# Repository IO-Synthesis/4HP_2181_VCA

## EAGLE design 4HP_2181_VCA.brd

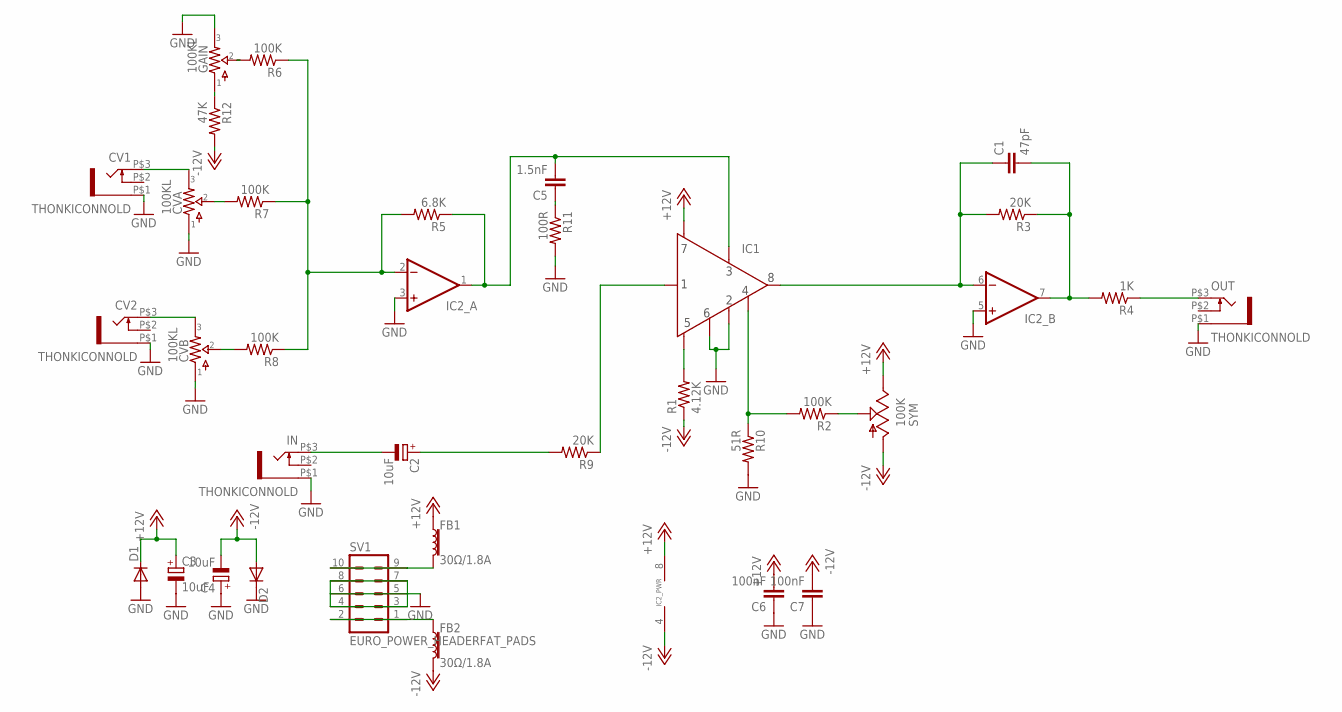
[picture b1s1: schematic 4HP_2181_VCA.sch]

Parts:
C1: 47pF; 0603-CAP
C2, C3, C4: 10uF; CASE_B
C5: 1.5nF; 0603-CAP
C6, C7: 100nF; 0603-CAP
CV1, CV2: THONKICONNOLD; THONKICONN
CVA: 100KL; 9MM_W/MOUNTS-2MMHOLES
CVB: 100KL; 9MM_W/MOUNTS-2MMHOLES
D1, D2: DIODE-SOD-123; SOD-123
FB1, FB2: 30Ω/1.8A; 0603
GAIN: 100KL; 9MM_W/MOUNTS-2MMHOLES
IC1: THAT2181C; SIL8
IC2: DUALSMD; SO08
IN: THONKICONNOLD; THONKICONN
OUT: THONKICONNOLD; THONKICONN
R1: 4.12K; 0603-RES
R2, R6, R7, R8: 100K; 0603-RES
R3, R9: 20K; 0603-RES
R4: 1K; 0603-RES
R5: 6.8K; 0603-RES
R10: 51R; 0603-RES
R11: 100R; 0603-RES
R12: 47K; 0603-RES
SV1: EURO_POWER_HEADERFAT_PADS; EURO_PWR_HEADER_FAT
SYM: 100K; S64W

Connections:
+12V: C3.+, C6.2, D1.C, FB1.1, IC1.7, IC2.8 (V+), SYM.E
-12V: C4.-, C7.2, D2.A, FB2.2, IC2.4 (V-), R1.1, R12.2, SYM.A
GND: C3.-, C4.+, C6.1, C7.1, CV1.P$1 (5), CV2.P$1 (5), CVA.P$1 (1), CVB.P$1 (1), D1.A, D2.C, GAIN.P$3 (3), IC1.2, IC1.6, IC2.3 (+IN), IC2.5 (+IN), IN.P$1 (5), OUT.P$1 (5), R10.2, R11.2, SV1.3, SV1.4, SV1.5, SV1.6, SV1.7, SV1.8
unnamed: C1.1, IC1.8, IC2.6 (-IN), R3.2
unnamed: C5.2, IC1.3, IC2.1 (OUT), R5.1
unnamed: IC1.5, R1.2
unnamed: C1.2, IC2.7 (OUT), R3.1, R4.2
unnamed: IC1.4, R2.2, R10.1
unnamed: R2.1, SYM.S
unnamed: OUT.P$3 (3), R4.1
unnamed: GAIN.P$2 (2), R6.2
unnamed: CVA.P$2 (2), R7.2
unnamed: CVB.P$2 (2), R8.2
unnamed: IC2.2 (-IN), R5.2, R6.1, R7.1, R8.1
unnamed: C2.+, R9.2
unnamed: C2.-, IN.P$3 (3)
unnamed: IC1.1, R9.1
unnamed: CV1.P$3 (3), CVA.P$3 (3)
unnamed: CV2.P$3 (3), CVB.P$3 (3)
unnamed: FB1.2, SV1.9, SV1.10
unnamed: FB2.1, SV1.1, SV1.2
unnamed: C5.1, R11.1
unnamed: GAIN.P$1 (1), R12.1

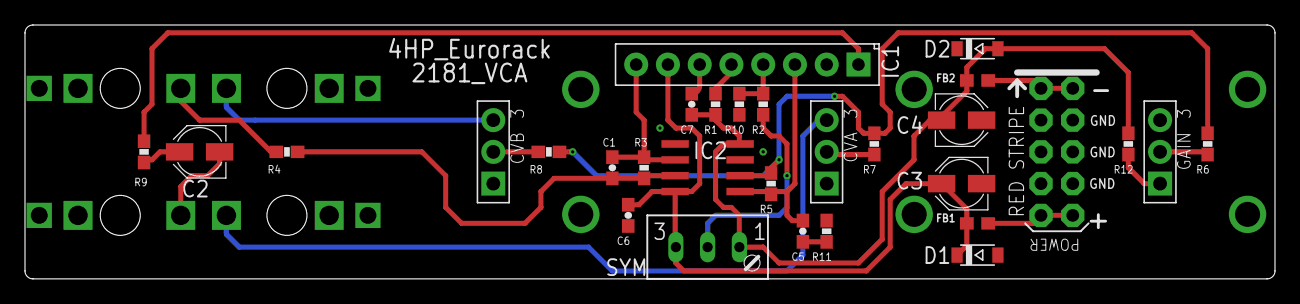
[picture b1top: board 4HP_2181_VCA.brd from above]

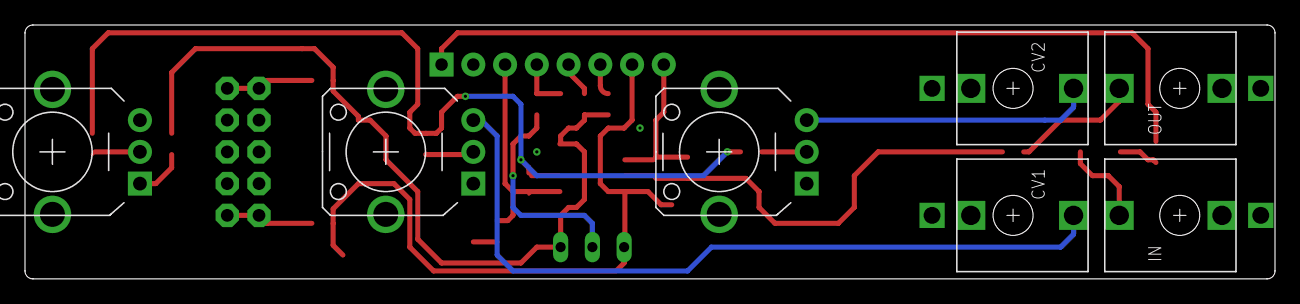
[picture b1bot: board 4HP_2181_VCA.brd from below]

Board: 2 copper layers, 100.0 x 20.3 mm, 34 parts (4 on the bottom side), 23 nets.

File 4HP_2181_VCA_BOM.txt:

Partlist exported from C:/Users/Erik/Documents/GitHub/4HP_2181_VCA/4HP_2181_VCA.sch at 4/30/2017 8:24 AM

Part Value                     Device                    Package               Description                                       PROD_ID    VALUE   
C1   47pF                      CAP0603-CAP               0603-CAP              Capacitor                                                            
C2   10uF                      CAPACITOR_POL-CASE_B      CASE_B                Polarized capacitor in various packages                              
C3   10uF                      CAPACITOR_POL-CASE_B      CASE_B                Polarized capacitor in various packages                              
C4   10uF                      CAPACITOR_POL-CASE_B      CASE_B                Polarized capacitor in various packages                              
C5   1.5nF                     CAP0603-CAP               0603-CAP              Capacitor                                                            
C6   100nF                     CAP0603-CAP               0603-CAP              Capacitor                                                            
C7   100nF                     CAP0603-CAP               0603-CAP              Capacitor                                                            
CV1  THONKICONNOLD             THONKICONNOLD             THONKICONN            3.5mm socket for Eurorack modular synths                             
CV2  THONKICONNOLD             THONKICONNOLD             THONKICONN            3.5mm socket for Eurorack modular synths                             
CVA  100KL                     POTS9MM_MOUNTED_2MMH      9MM_W/MOUNTS-2MMHOLES                                                                      
CVB  100KL                     POTS9MM_MOUNTED_2MMH      9MM_W/MOUNTS-2MMHOLES                                                                      
D1                             DIODE-SOD-123             SOD-123               Various Diode Packages                                               
D2                             DIODE-SOD-123             SOD-123               Various Diode Packages                                               
FB1  30O/1.8A                  FERRITE_BEAD-0603         0603                  Ferrite Bead (blocks, cores, rings, chokes, etc.) NDUC-07859 30O/1.8A
FB2  30O/1.8A                  FERRITE_BEAD-0603         0603                  Ferrite Bead (blocks, cores, rings, chokes, etc.) NDUC-07859 30O/1.8A
GAIN 100KL                     POTS9MM_MOUNTED_2MMH      9MM_W/MOUNTS-2MMHOLES                                                                      
IC1                            THAT2181C                 SIL8                                                                                       
IC2                            DUALSMD                   SO08                  OP AMP                                                               
IN   THONKICONNOLD             THONKICONNOLD             THONKICONN            3.5mm socket for Eurorack modular synths                             
OUT  THONKICONNOLD             THONKICONNOLD             THONKICONN            3.5mm socket for Eurorack modular synths                             
R1   4.12K                     RESISTOR0603-RES          0603-RES              Resistor                                                             
R2   100K                      RESISTOR0603-RES          0603-RES              Resistor                                                             
R3   20K                       RESISTOR0603-RES          0603-RES              Resistor                                                             
R4   1K                        RESISTOR0603-RES          0603-RES              Resistor                                                             
R5   6.8K                      RESISTOR0603-RES          0603-RES              Resistor                                                             
R6   100K                      RESISTOR0603-RES          0603-RES              Resistor                                                             
R7   100K                      RESISTOR0603-RES          0603-RES              Resistor                                                             
R8   100K                      RESISTOR0603-RES          0603-RES              Resistor                                                             
R9   20K                       RESISTOR0603-RES          0603-RES              Resistor                                                             
R10  51R                       RESISTOR0603-RES          0603-RES              Resistor                                                             
R11  100R                      RESISTOR0603-RES          0603-RES              Resistor                                                             
R12  47K                       RESISTOR0603-RES          0603-RES              Resistor                                                             
SV1  EURO_POWER_HEADERFAT_PADS EURO_POWER_HEADERFAT_PADS EURO_PWR_HEADER_FAT   Power Header                                                         
SYM  100K                      TRIM_US-S64W              S64W                  POTENTIOMETER

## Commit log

2017-01-13 :neckbeard: Added .gitattributes & .gitignore files
2017-05-11 4HP 2181 VCA
2017-05-21 4HP 2181 VCA Panel

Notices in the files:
parts and their libraries:
SparkFun-Passives: Licensing: Creative Commons ShareAlike 4.0 International - https://creativecommons.org/licenses/by-sa/4.0
